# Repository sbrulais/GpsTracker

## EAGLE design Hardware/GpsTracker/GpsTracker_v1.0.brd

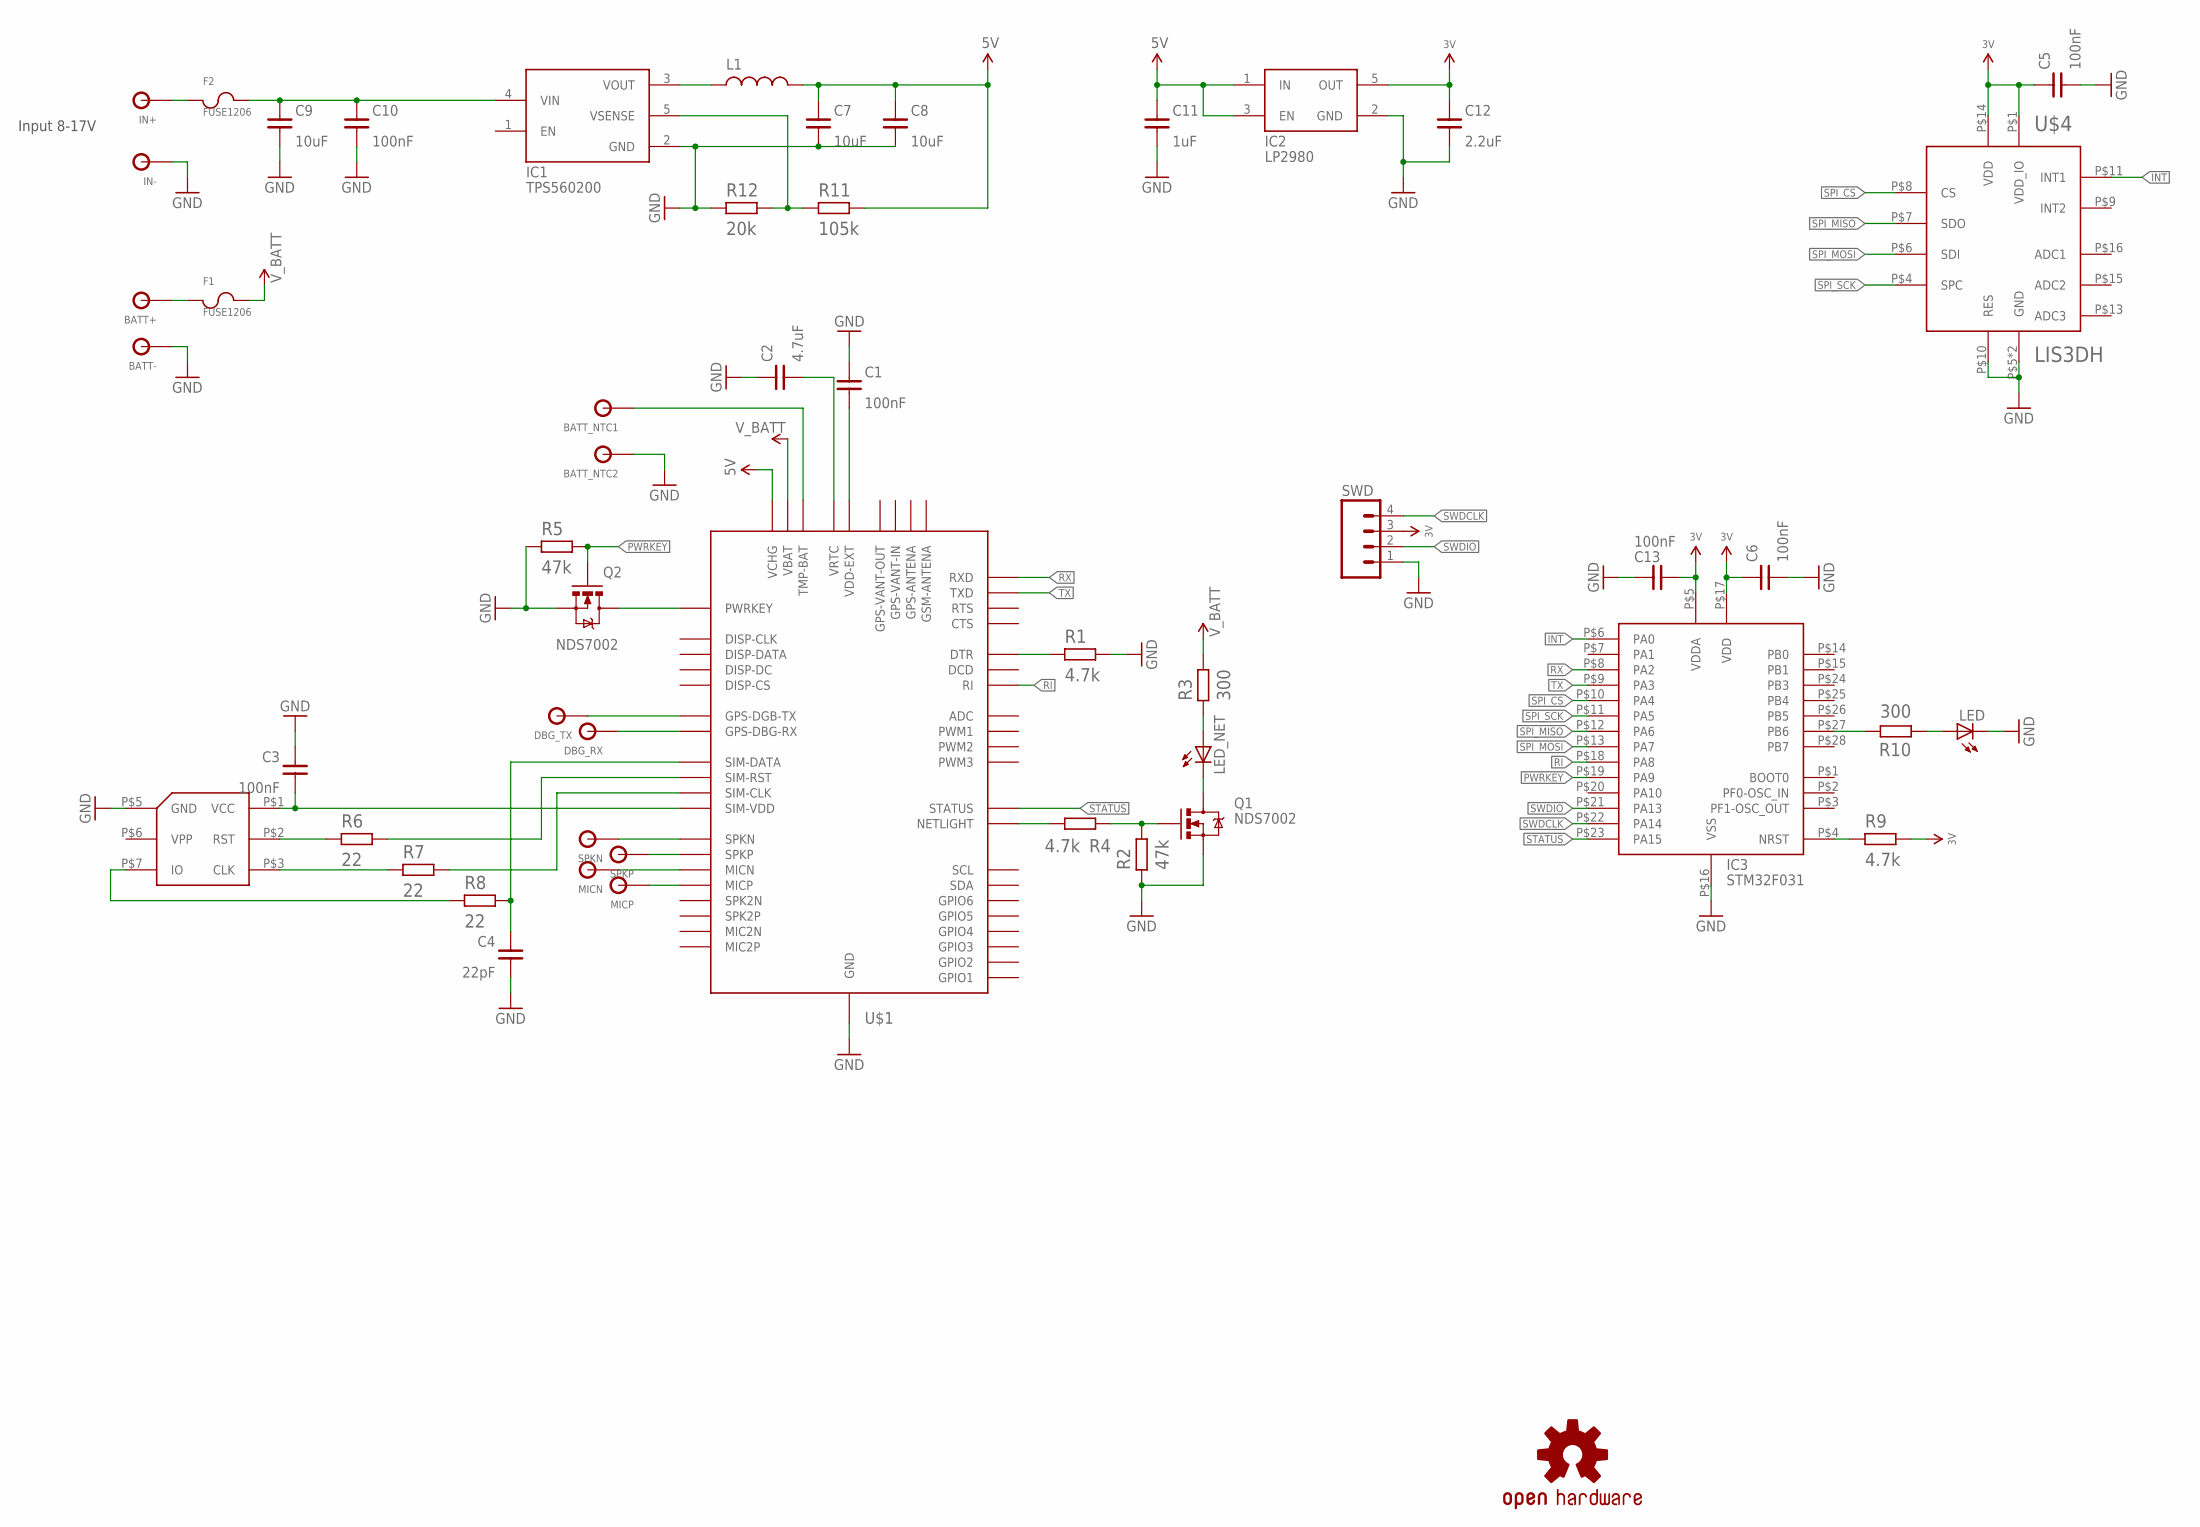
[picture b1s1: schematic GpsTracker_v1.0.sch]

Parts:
BATT+: TEST_POINT_SMD
BATT-: TEST_POINT_SMD
BATT_NTC1, BATT_NTC2: TEST_POINT_R04; TP_R04
C1, C3, C5, C6, C10, C13: 100nF; R0603
C2: 4.7uF; R0805
C4: 22pF; R0603
C7, C8: 10uF; R0805
C9: 10uF; 1206
C11: 1uF; R0805
C12: 2.2uF; R0805
DBG_RX: TEST_POINT_R04; TP_R04
DBG_TX: TEST_POINT_R04; TP_R04
F1, F2: FUSE1206; 1206
IC1: TPS560200; SOT23-5L
IC2: LP2980; SOT23-5L
IC3: STM32F031; UFQFPN28
IN+: TEST_POINT_SMD
IN-: TEST_POINT_SMD
L1: LNRG_4026; NRG_4026
LED: LED0603; LED-0603
LED_NET: LED0603; LED-0603
LOGO1: OSHW-LOGOS; OSHW-LOGO-S
MICN: TEST_POINT_R04; TP_R04
MICP: TEST_POINT_R04; TP_R04
Q1, Q2: NDS7002; SOT23
R1, R4, R9: 4.7k; R0603
R2, R5: 47k; R0603
R3, R10: 300; R0603
R6, R7, R8: 22; R0603
R11: 105k; R0603
R12: 20k; R0603
SPKN: TEST_POINT_R04; TP_R04
SPKP: TEST_POINT_R04; TP_R04
SWD: M041.27MM; 1X04-1.27MM
U$1: SIM908
U$3: SIM_CARD; SIM_SAMSUNG
U$4: LIS3DH; LGA16D

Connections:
3V: C5.2, C6.2, C12.2, C13.2, IC2.5 (OUT), IC3.P$5 (VDDA), IC3.P$17 (VDD), R9.2, SWD.3, U$4.P$1 (VDD_IO), U$4.P$14 (VDD)
5V: C7.2, C8.2, C11.2, IC2.1 (IN), IC2.3 (EN), L1.P$2 (2), R11.2, U$1.VCHG
GND: BATT-.P$1, BATT_NTC2.P$1, C1.2, C2.2, C3.2, C4.1, C5.1, C6.1, C7.1, C8.1, C9.1, C10.1, C11.1, C12.1, C13.1, IC1.2 (GND), IC2.2 (GND), IC3.P$16 (VSS), IN-.P$1, LED.C, Q1.2 (S), Q2.2 (S), R1.2, R2.1, R5.1, R12.1, SWD.1, U$1.GND, U$1.GND2 (GND), U$1.GND3 (GND), U$1.GND4 (GND), U$1.GND5 (GND), U$1.GND6 (GND), U$1.GND7 (GND), U$1.GND8 (GND), U$1.GND9 (GND), U$1.GND10 (GND), U$1.GND11 (GND), U$1.GND12 (GND), U$1.GND13 (GND), U$1.GND14 (GND), U$1.GND15 (GND), U$1.GND16 (GND), U$1.GND17 (GND), U$1.GND18 (GND), U$3.P$5 (GND), U$4.P$5 (GND), U$4.P$10 (RES), U$4.P$12 (GND)
INT: IC3.P$6 (PA0), U$4.P$11 (INT1)
unnamed: R1.1, U$1.DTR
unnamed: C1.1, U$1.VDD-EXT
unnamed: C2.1, U$1.VRTC
unnamed: BATT_NTC1.P$1, U$1.TEMP-BAT (TMP-BAT)
unnamed: Q1.1 (G), R2.2, R4.1
unnamed: LED_NET.C, Q1.3 (D)
unnamed: LED_NET.A, R3.1
unnamed: Q2.3 (D), U$1.PWRKEY
unnamed: R4.2, U$1.NETLIGHT
unnamed: DBG_RX.P$1, U$1.GPS-DBG-RXD (GPS-DBG-RX)
unnamed: C3.1, U$1.SIM-VDD, U$3.P$1 (VCC)
unnamed: R6.1, U$3.P$2 (RST)
unnamed: R7.1, U$3.P$3 (CLK)
unnamed: R6.2, U$1.SIM-RST
unnamed: R7.2, U$1.SIM-CLK
unnamed: R8.1, U$3.P$7 (IO)
unnamed: C4.2, R8.2, U$1.SIM-DATA
unnamed: DBG_TX.P$1, U$1.GPS-DBG-TXD (GPS-DGB-TX)
unnamed: SPKN.P$1, U$1.SPK1N (SPKN)
unnamed: SPKP.P$1, U$1.SPK1P (SPKP)
unnamed: MICN.P$1, U$1.MIC1N (MICN)
unnamed: MICP.P$1, U$1.MIC1P (MICP)
unnamed: BATT+.P$1, F1.1
unnamed: IC3.P$4 (NRST), R9.1
unnamed: IC3.P$27 (PB6), R10.2
unnamed: LED.A, R10.1
unnamed: IC1.3 (VOUT), L1.P$1 (1)
unnamed: C9.2, C10.2, F2.2, IC1.4 (VIN)
unnamed: IC1.5 (VSENSE), R11.1, R12.2
unnamed: F2.1, IN+.P$1
PWRKEY: IC3.P$19 (PA9), Q2.1 (G), R5.2
RI: IC3.P$18 (PA8), U$1.RI
RX: IC3.P$8 (PA2), U$1.RXD
SPI_CS: IC3.P$10 (PA4), U$4.P$8 (CS)
SPI_MISO: IC3.P$12 (PA6), U$4.P$7 (SDO)
SPI_MOSI: IC3.P$13 (PA7), U$4.P$6 (SDI)
SPI_SCK: IC3.P$11 (PA5), U$4.P$4 (SPC)
STATUS: IC3.P$23 (PA15), U$1.STATUS
SWDCLK: IC3.P$22 (PA14), SWD.4
SWDIO: IC3.P$21 (PA13), SWD.2
TX: IC3.P$9 (PA3), U$1.TXD
V_BATT: F1.2, R3.2, U$1.VBAT, U$1.VBAT2 (VBAT)

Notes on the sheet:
Input 8-17V

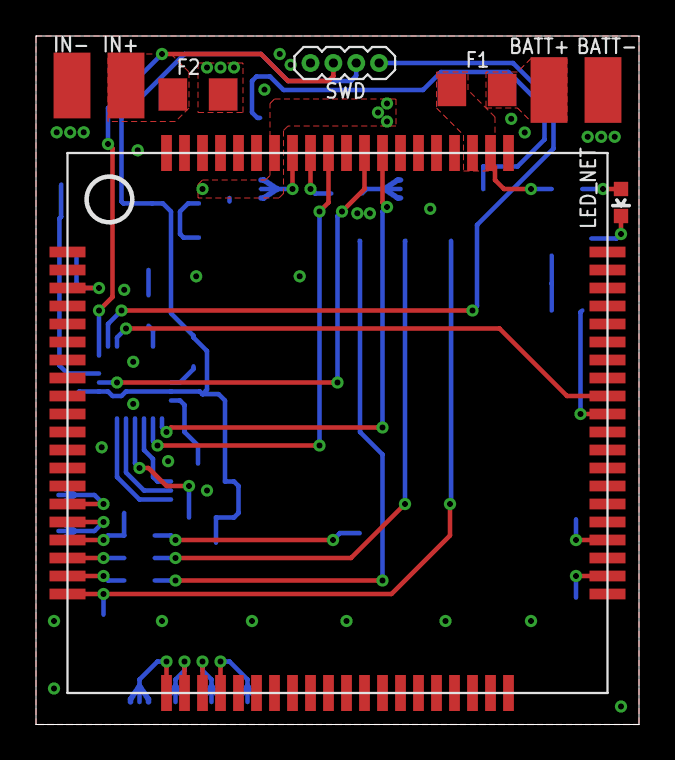
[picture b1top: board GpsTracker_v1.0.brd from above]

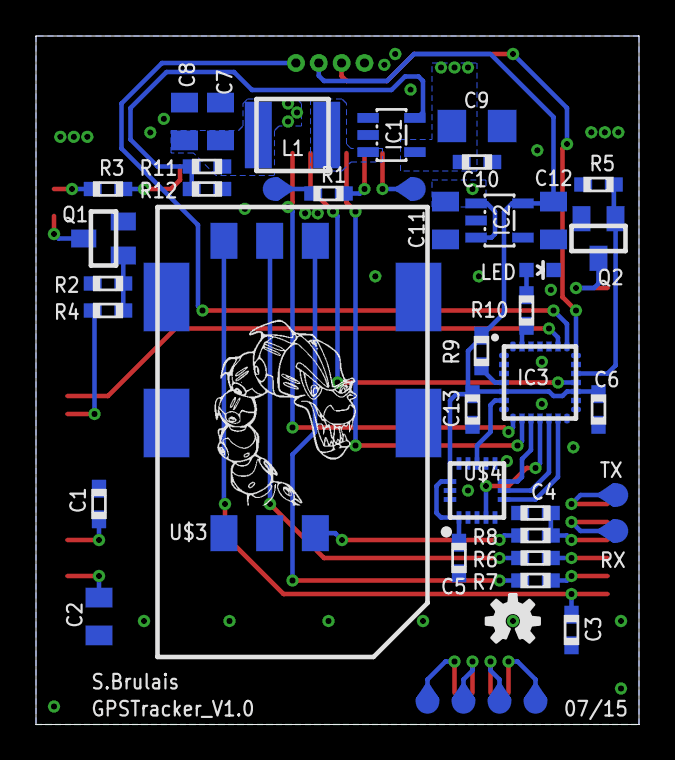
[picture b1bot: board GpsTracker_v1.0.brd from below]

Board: 2 copper layers, 33.5 x 38.2 mm, 52 parts (43 on the bottom side), 46 nets.

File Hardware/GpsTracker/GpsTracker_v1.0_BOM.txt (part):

Partlist exported from C:/Users/SB233390/Documents/Work/MySVN/GpsTracker/Hardware/GpsTracker/GpsTracker_v1.0.sch at 27/07/2015 10:06:30

Qty Value          Device         Package        Parts                                                        Description                                                                                                                                                                                                        
2                  LED0603        LED-0603       LED, LED_NET                                                 LEDs                                                                                                                                                                                                               
1                  LNRG_4026      NRG_4026       L1                                                                                                                                                                                                                                                                              
1                  M041.27MM      1X04-1.27MM    SWD                                                          Header 4                                                                                                                                                                                                           
6   100nF          C0603          R0603          C1, C3, C5, C6, C10, C13                                                                                                                                                                                                                                                        
1   105k           R0603          R0603          R11                                                                                                                                                                                                                                                                             
2   10uF           C0805          R0805          C7, C8                                                                                                                                                                                                                                                                          
1   10uF           C1206          1206           C9                                                                                                                                                                                                                                                                              
1   1uF            C0805          R0805          C11                                                                                                                                                                                                                                                                             
1   2.2uF          C0805          R0805          C12                                                                                                                                                                                                                                                                             
1   20k            R0603          R0603          R12                                                                                                                                                                                                                                                                             
3   22             R0603          R0603          R6, R7, R8                                                                                                                                                                                                                                                                      
1   22pF           C0603          R0603          C4                                                                                                                                                                                                                                                                              
2   300            R0603          R0603          R3, R10                                                                                                                                                                                                                                                                         
3   4.7k           R0603          R0603          R1, R4, R9                                                                                                                                                                                                                                                                      
1   4.7uF          C0805          R0805          C2                                                                                                                                                                                                                                                                              
2   47k            R0603          R0603          R2, R5                                                                                                                                                                                                                                                                          
2   FUSE1206       FUSE1206       1206           F1, F2                                                                                                                                                                                                                                                                          
1   LIS3DH         LIS3DH         LGA16D         U$4                                                          MEMS digital output motion sensor                                                                                                                                                                                  
1   LP2980         LP2980         SOT23-5L       IC2                                                                                                                                                                                                                                                                             
2   NDS7002        NDS7002        SOT23          Q1, Q2                                                                                                                                                                                                                                                                          
1   OSHW-LOGOS     OSHW-LOGOS     OSHW-LOGO-S    LOGO1                                                        Open Source Hardware Logo This logo indicates the piece of hardware it is found on incorporates a OSHW license and/or adheres to the definition of open source hardware found here: http://freedomdefined.org/OSHW 
1   SIM908         SIM908         SIM908         U$1                                                                                                                                                                                                                                                                             
1   SIM_CARD       SIM_CARD       SIM_SAMSUNG    U$3                                                                                                                                                                                                                                                                             
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
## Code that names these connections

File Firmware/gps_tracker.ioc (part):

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Mcu.Name=STM32F031G(4-6)Ux
Mcu.Package=UFQFPN28
Mcu.UserName=STM32F031G4Ux
PA0.Signal=GPXTI0
PA15.Signal=GPIO_Input
PA2.Signal=USART1_TX
PA3.Signal=USART1_RX
PA4.Signal=SPI1_NSS
PA5.Signal=SPI1_SCK
PA6.Signal=SPI1_MISO
PA7.Signal=SPI1_MOSI
PA8.Signal=GPIO_Input
PA9.Signal=GPIO_Input
PB6.Signal=GPIO_Output
RCC.SYSCLKFreq_VALUE=8000000

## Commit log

2015-09-23 :octocat: Added .gitattributes & .gitignore files
2015-12-04 Firmware update, UART need to be debugged

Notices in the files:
parts and their libraries:
SparkFun-Passives: Licensing: Creative Commons ShareAlike 4.0 International - https://creativecommons.org/licenses/by-sa/4.0
